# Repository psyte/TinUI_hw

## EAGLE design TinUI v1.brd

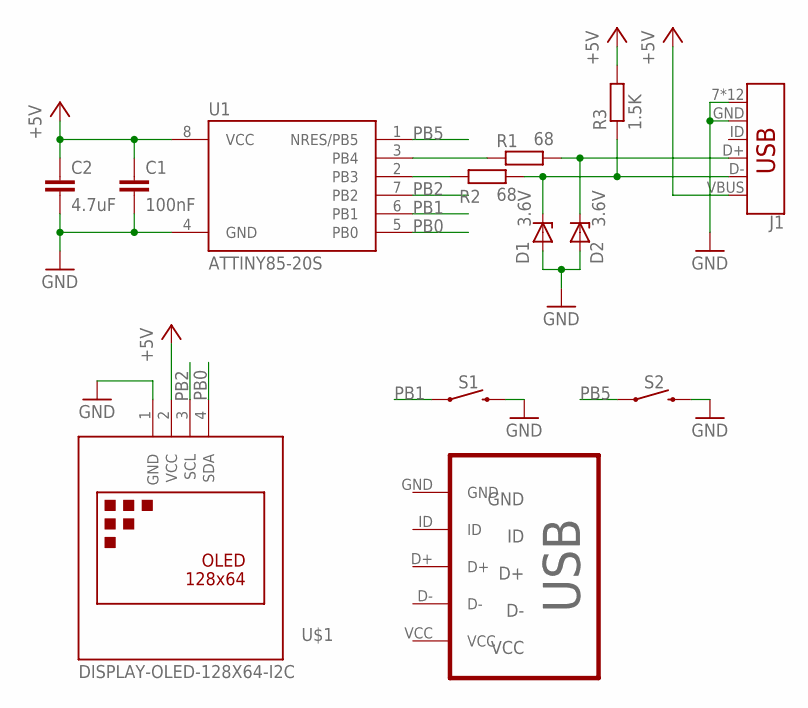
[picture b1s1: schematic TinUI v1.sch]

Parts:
C1: 100nF; C0603
C2: 4.7uF; C0603
D1, D2: 3.6V; SOD80C
J1: AMP FCI 10103594-0001LF; USB-MICROB-PTH
R1, R2: 68; R0603
R3: 1.5K; R0603
S1, S2: MOMENTARY-SWITCH-SPST-SMD-6.0X3.5MM; TACTILE_SWITCH_SMD_6.0X3.5MM
U1: ATTINY85-20S; SOIC8_EIAJ_208MIL
U$1: DISPLAY-OLED-128X64-I2C
U$2: MICRO-USB-B; MICRO_USB_4_LEGS

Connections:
+5V: C1.1, C2.1, J1.VBUS, R3.2, U1.8 (VCC), U$1.2 (VCC)
GND: C1.2, C2.2, D1.A, D2.A, J1.7 (SHIELD), J1.GND, J1.SHEILD2 (SHIELD), J1.SHIELD, J1.SHIELD3 (SHIELD), J1.SHIELD4 (SHIELD), J1.SHIELD5 (SHIELD), J1.SHIELD6 (SHIELD), J1.SHIELD8 (SHIELD), J1.SHIELD9 (SHIELD), J1.SHIELD10 (SHIELD), J1.SHIELD11 (SHIELD), J1.SHIELD12 (SHIELD), S1.2, S2.2, U1.4 (GND), U$1.1 (GND)
unnamed: R1.1, U1.3 (PB4)
unnamed: R2.1, U1.2 (PB3)
unnamed: D2.C, J1.D+, R1.2
unnamed: D1.C, J1.D-, R2.2, R3.1
PB0: U1.5 (PB0), U$1.4 (SDA)
PB1: S1.1, U1.6 (PB1)
PB2: U1.7 (PB2), U$1.3 (SCL)
PB5: S2.1, U1.1 (NRES/PB5)

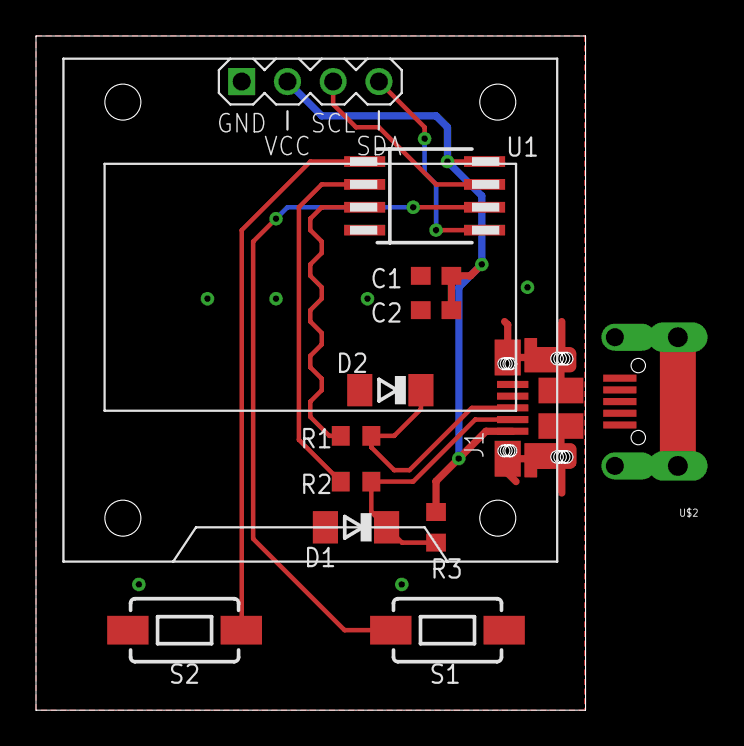
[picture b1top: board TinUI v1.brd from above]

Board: 2 copper layers, 30.5 x 37.5 mm, 13 parts (0 on the bottom side), 10 nets.

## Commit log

2018-12-04 Removed backup files

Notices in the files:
parts and their libraries:
SparkFun-Connectors: Licensing: Creative Commons ShareAlike 4.0 International - https://creativecommons.org/licenses/by-sa/4.0
diy-modules: Released under the Creative Commons Attribution 4.0 International License: http://creativecommons.org/licenses/by/4.0
